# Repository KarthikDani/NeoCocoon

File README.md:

# InfantIncubator

Hardware procurement:
- [Final BOM Link](https://docs.google.com/spreadsheets/d/1u5Mlvxa6RhjDjX_Zx-iyKGHfaelGLQUbIJbQIuBkTXc/edit?gid=1763511828#gid=1763511828)

References:
- [Tx/Rx Reference - Medium article](https://medium.com/geekculture/serial-connection-between-raspberry-pi-and-raspberry-pico-d6c0ba97c7dc)
- [Pinout Guide for RPI](https://pinout.xyz/)
- [Pico datasheet](https://datasheets.raspberrypi.com/pico/pico-2-datasheet.pdf)

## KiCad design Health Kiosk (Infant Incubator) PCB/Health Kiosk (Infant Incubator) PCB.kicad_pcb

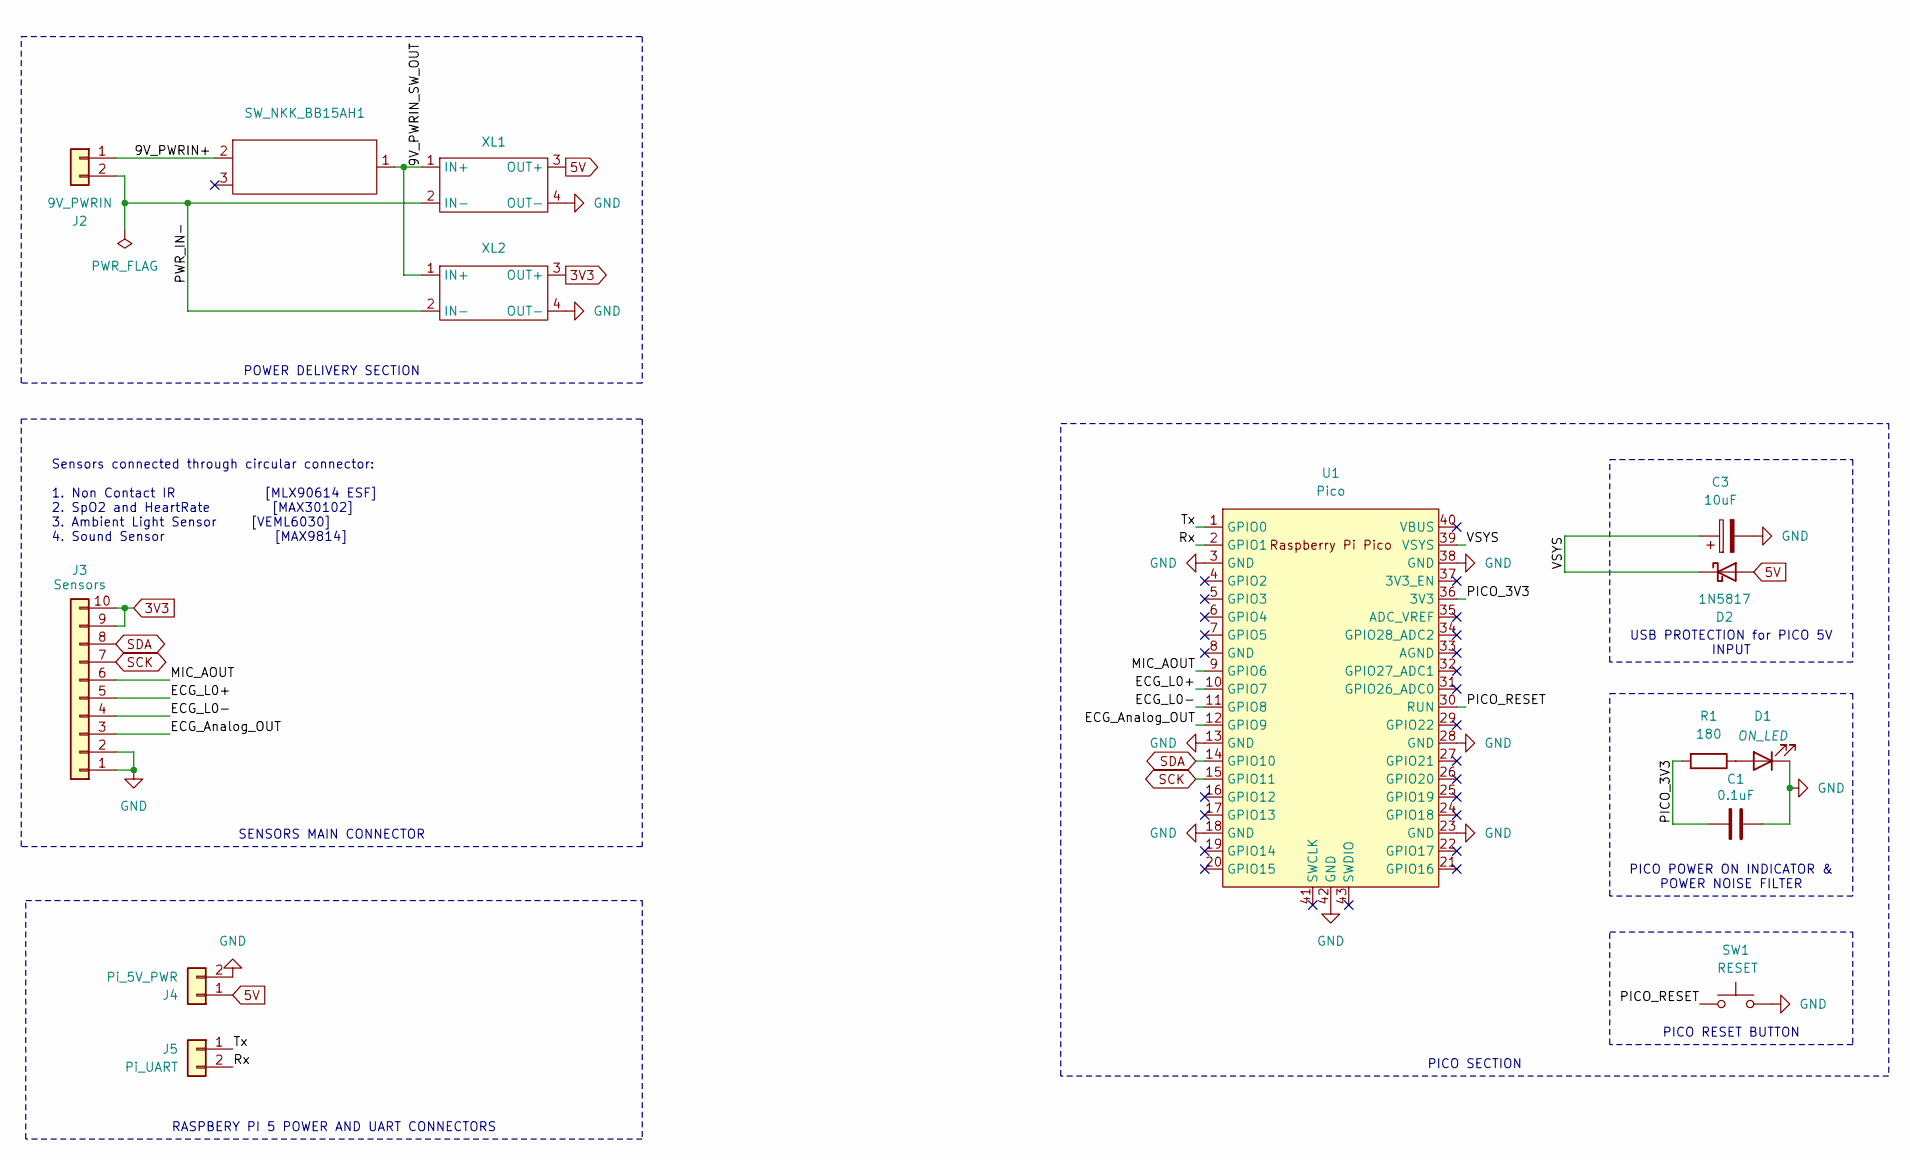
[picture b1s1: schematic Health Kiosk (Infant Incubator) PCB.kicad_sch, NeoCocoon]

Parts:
C1: 0.1uF; C_Disc_D10.5mm_W5.0mm_P5.00mm
C3: 10uF; CP_Radial_D5.0mm_P2.50mm
D1: ON_LED; LED_Rectangular_W5.0mm_H2.0mm_Horizontal_O1.27mm_Z1.0mm
D2: 1N5817; D_DO-41_SOD81_P10.16mm_Horizontal
J2: 9V_PWRIN; JST_XH_S2B-XH-A-1_1x02_P2.50mm_Horizontal
J3: Sensors; JST_XH_S10B-XH-A-1_1x10_P2.50mm_Horizontal
J4: Pi_5V_PWR; JST_XH_S2B-XH-A-1_1x02_P2.50mm_Horizontal
J5: Pi_UART; JST_XH_S2B-XH-A-1_1x02_P2.50mm_Horizontal
R1: 180; R_Axial_DIN0207_L6.3mm_D2.5mm_P7.62mm_Horizontal
SW1: RESET; SW_SPST_Omron_B3FS-105xP
SW_NKK_BB15AH1: SW_NKK_BB15AH
U1: Pico; RPi_Pico_SMD_TH
XL1, XL2: XL4015

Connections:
3V3: J3.9, J3.10, XL2.3 (OUT+)
5V: D2.2 (A), J4.1, XL1.3 (OUT+)
/9V_PWRIN+: J2.1, SW_NKK_BB15AH1.2
/9V_PWRIN_SW_OUT: SW_NKK_BB15AH1.1, XL1.1 (IN+), XL2.1 (IN+)
/ECG_Analog_OUT: J3.3, U1.12 (GPIO9)
/ECG_L0+: J3.5, U1.10 (GPIO7)
/ECG_L0-: J3.4, U1.11 (GPIO8)
/MIC_AOUT: J3.6, U1.9 (GPIO6)
/PICO_3V3: C1.1, R1.2, U1.36 (3V3)
/PICO_RESET: SW1.1, U1.30 (RUN)
/PWR_IN-: J2.2, XL1.2 (IN-), XL2.2 (IN-)
/Rx: J5.2, U1.2 (GPIO1)
/Tx: J5.1, U1.1 (GPIO0)
/VSYS: C3.1, D2.1 (K), U1.39 (VSYS)
GND: C1.2, C3.2, D1.1 (K), J3.1, J3.2, J4.2, SW1.2, U1.3 (GND), U1.13 (GND), U1.18 (GND), U1.23 (GND), U1.28 (GND), U1.38 (GND), U1.42 (GND), XL1.4 (OUT-), XL2.4 (OUT-)
unnamed: D1.2 (A), R1.1
SCK: J3.7, U1.15 (GPIO11)
SDA: J3.8, U1.14 (GPIO10)

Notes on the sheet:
PICO SECTION
PICO RESET BUTTON
PICO POWER ON INDICATOR & POWER NOISE FILTER
POWER DELIVERY SECTION
SENSORS MAIN CONNECTOR
RASPBERY PI 5 POWER AND UART CONNECTORS
USB PROTECTION for PICO 5V INPUT
Sensors connected through circular connector: 1. Non Contact IR [MLX90614 ESF] 2. SpO2 and HeartRate [MAX30102] 3. Ambient Light Sensor [VEML6030] 4. Sound Sensor [MAX9814]

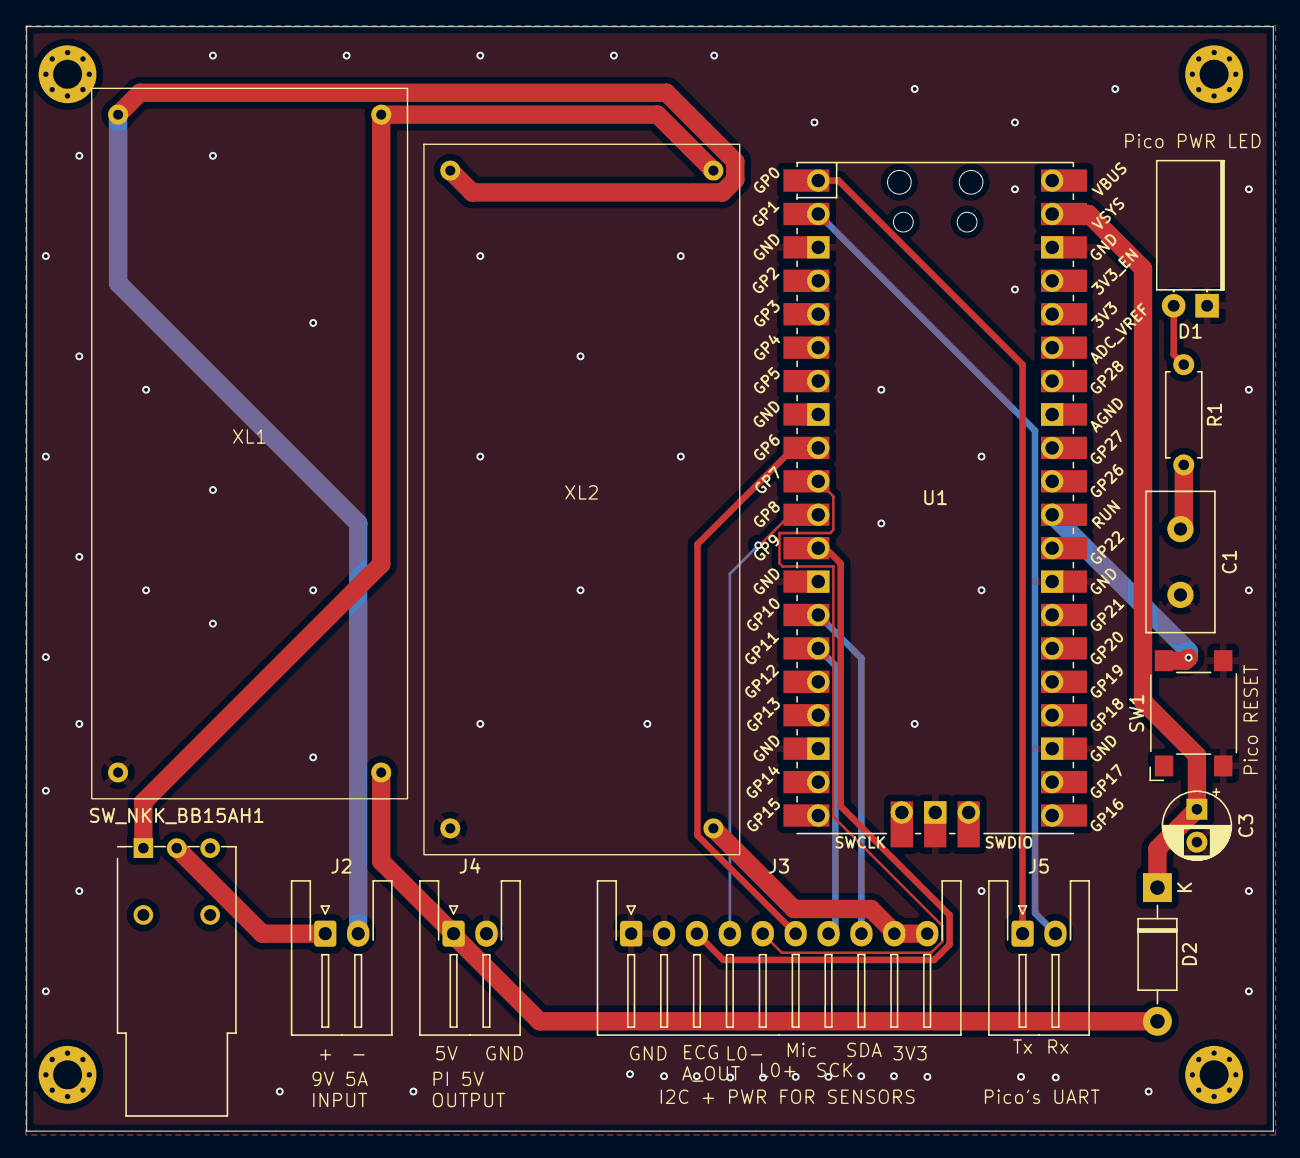
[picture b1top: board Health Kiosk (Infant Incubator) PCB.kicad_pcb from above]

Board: 2 copper layers, 94.8 x 83.9 mm, 14 parts (0 on the bottom side), 18 nets.

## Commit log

2024-08-25 Notes Extractor for Literature
2024-08-25 WHO Literature Highlighted
2024-09-02 viz added for test
2024-09-04 Features and Alarms done. Specs remaining
2024-09-07 All the points are ready for inquiry
2024-09-11 Mindmap folder added
2024-09-30 Added KiCAD Project
2024-09-30 pico and piconnections done. GPIOs pending
2024-10-11 PCB Design Finished (Buck footprint left)
2024-10-20 Synopsis, Literature Survey and UI fullscreen
2024-10-20 Synopsis Completed
2024-10-21 Authors added, Synopsis completed
